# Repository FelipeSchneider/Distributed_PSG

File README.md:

# Distributed_PSG
Final project of the Electrical Engineering course, made by Felipe Britto Azevedo Schneider. The goal of this project is to develop hardware and software capable of monitoring a patient thought the night with more comfort that is possible using the traditional method.
Article abstract:
The impairment of sleep quality directly rises the chances of heart attack, obesity, and strokes, among others, what makes the polysomnography (PSG) an important public health tool. However, the inherent problems with PSG makes the correct diagnosis of sleep diseases a difficult task. This work presents a distributed novel class III PSG system, composed of three boards, all together capable of monitoring simultaneously environmental variables and patient signals. This system reduces the distress of a PSG exam, dismiss the need for an overnight sleep in a health care/sleep center, facilitates a self-set-up and an internet based diagnosis. Methods: Design and implementation of two wearable and one bedside PCB boards that together are able to, synchronously, monitor, process and log into a microSD card environmental parameters (temperature, humidity, visible light intensity and audible noise level) together with patient signals (electrocardiogram, electrooculogram, body, and limbs position). Results: A novel class III PSG system with independent boards capable of operating for more than 16 hours powered by a 750 mAh, 3.7 V battery with 0.003% data loss during preliminary PSG exams. Additionally, a computer-based program capable of reading, decode and present the data in graphs was developed and is presented. Conclusion: This article contributes to the PSG research and with the development of new PSG systems as well as the improvement of patients comfort. All code and hardware here developed are open.

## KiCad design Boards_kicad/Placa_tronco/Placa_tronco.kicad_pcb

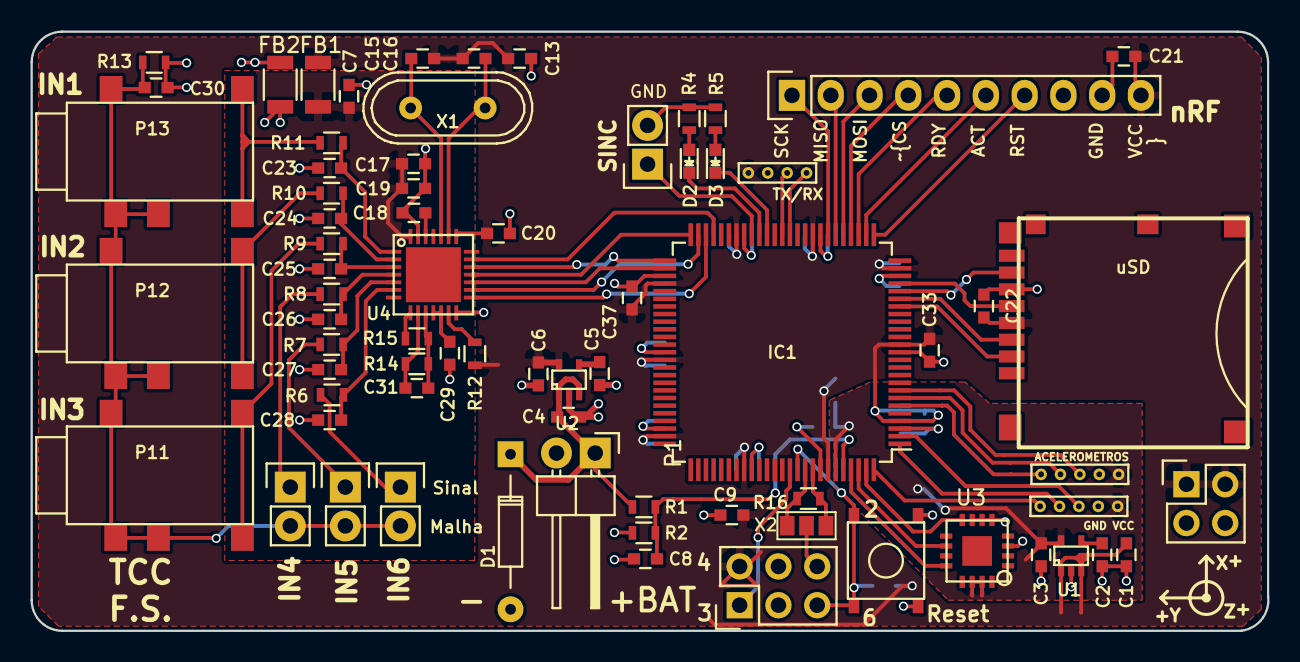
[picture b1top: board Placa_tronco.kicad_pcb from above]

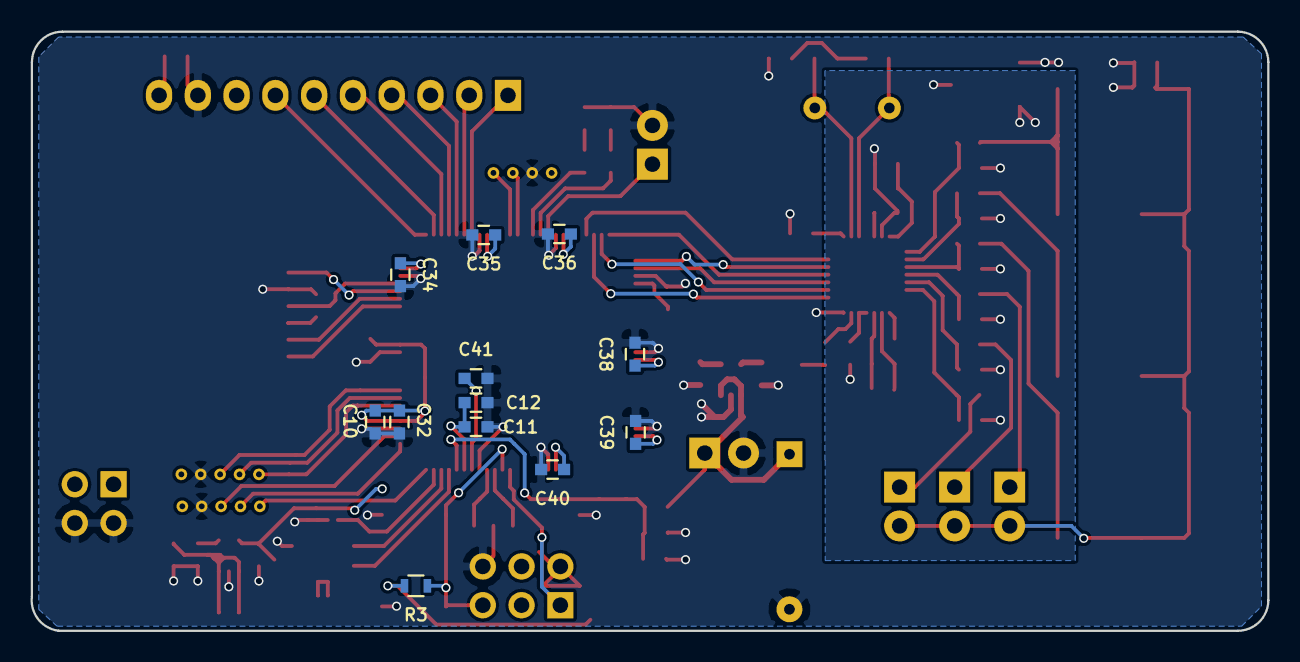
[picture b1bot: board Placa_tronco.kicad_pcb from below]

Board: 2 copper layers, 81.0 x 39.2 mm, 84 parts (12 on the bottom side), 67 nets.

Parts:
C1, C3, C4, C6, C7, C8: 1uF; C_0603
C2, C5, C11, C30: 10nF; C_0603
C9, C10, C17: 10u; C_0603
C12: 10uF; C_0603
C13, C19, C20, C29, C32, C33, C34, C35, C36, C37, C38, C39, C40, C41: 100n; C_0603
C15, C16: 22p; C_0603
C18: 1u; C_0603
C21, C22: 100nF; C_0603
C23, C24, C25, C26, C27, C28: Xn; C_0603
C31: 1.5n; C_0603
D1: Z 5.7V; Diode_DO-35_SOD27_Horizontal_RM10
D2, D3: LED; LED_0603
FB1, FB2: FILTER; R_1206
IC1: ATXMEGA128A1U-A; TQFP-100_14x14mm_Pitch0.5mm
P1: CONN_01X02; Pin_Header_Angled_1x02
P2: CONN_02X02; Pin_Header_Straight_2x02
P3: PDI; Pin_Header_Straight_2x03
P4, P5: Acelerometro; 5-pin-50mil
P6, P7, P8, P9: CONN_01X02; Pin_Header_Straight_1x02
P10: nRF8001 CON; Pin_Header_Straight_1x10
P11, P12, P13: MIC-CON-MONO; J2-connector
P14: CONN_01X04; 4-pin-50mil
R1, R2: 47k; R_0603
R3, R6, R7, R8, R9, R10, R11: 10K; R_0603
R4, R5: 220; R_0603
R12, R13, R14, R16: 1M; R_0603
R15: 100K; R_0603
SD1: uSD; uSD_5027_normal
SW1: SW_PUSH; 5mm-smd-button
U1: TPS71727; SC-70-5
U2: TPS71733; SC-70-5
U3: ADXL335; ADXL335_correto
U4: ADS1293; ADS1293-correto
X1: 4.096MHz; Crystal_HC49-U_Vertical
X2: CRISTAL_16MHz; CRISTAL_16Mhz

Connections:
+BAT: C4.2, D1.2, P1.1, R1.1, U2.1, U2.3
/ACT_nRF: IC1.27, P10.6
/ADCA_REF: C3.2, C11.2, C12.2, IC1.95, P4.1, P5.1, U1.5, U3.14, U3.15
/ADC_A1: C8.2, IC1.96, R1.2, R2.2
/ADC_A2: IC1.97, U3.12
/ADC_A3: IC1.98, U3.10
/ADC_A4: IC1.99, U3.8
/ADC_A5: IC1.100, P4.5
/ADC_A6: IC1.1, P4.4
/ADC_A7: IC1.2, P4.3
/ADC_B1: IC1.6, P5.5
/ADC_B2: IC1.7, P5.4
/ADC_B3: IC1.8, P5.3
/MISO_nRF: IC1.31, P10.2
/MISO_uSD: IC1.21, SD1.7
/MOSI-uSD: IC1.20, SD1.3
/MOSI_nRF: IC1.30, P10.3
/RDY_nRF: IC1.28, P10.5
/RESET: IC1.90, P3.5, R3.1, SW1.2
/RST_nRF: IC1.26, P10.7
/SCK-uSD: IC1.22, SD1.5
/SCK_nRF: IC1.32, P10.1
/malha: C30.2, P7.2, P8.2, P9.2, P11.1, P11.2, P11.5, P12.1, P12.2, P12.5, P13.1, P13.2, P13.5, R13.2
/xt1: IC1.91, R16.2, X2.1
/xt2: IC1.92, R16.1, X2.3
/~CS_nRF: IC1.29, P10.4
/~SS-uSD: IC1.19, SD1.2
GND: C1.1, C2.1, C3.1, C4.1, C5.1, C6.1, C8.1, C9.2, C10.2, C11.1, C12.1, C13.1, C20.2, C21.1, C22.1, C30.1, C32.2, C33.2, C34.2, C35.2, C36.2, C37.2, C38.2, C39.2, C40.2, C41.2, D1.1, FB2.1, IC1.3, IC1.13, IC1.23, IC1.33, IC1.43, IC1.53, IC1.63, IC1.73, IC1.84, IC1.93, P1.2, P2.3, P2.4, P3.6, P4.2, P5.2, P6.2, P10.9, P14.2, R2.1, R4.1, R5.1, R13.1, SD1.6, SW1.1, U1.2, U2.2, U3.3, U3.5, U3.6, U3.7, U4.14, X2.2
GNDA: C7.1, C17.2, C18.1, C19.2, C23.2, C24.2, C25.2, C26.2, C27.2, C28.2, C29.2, FB2.2, U4.27
unnamed: C2.2, U1.4
unnamed: C5.2, U2.4
unnamed: C15.2, U4.24, X1.2
unnamed: C16.2, U4.23, X1.1
unnamed: C18.2, U4.26
unnamed: C23.1, R11.1, U4.1
unnamed: C24.1, R10.1, U4.2
unnamed: C25.1, R9.1, U4.3
unnamed: C26.1, R8.1, U4.4
unnamed: C27.1, R7.1, U4.5
unnamed: C28.1, R6.1, U4.6
unnamed: C29.1, U4.11, U4.12
unnamed: C31.1, R14.1, R15.1, U4.10
unnamed: C31.2, R14.2, U4.9
unnamed: D2.1, IC1.41
unnamed: D2.2, R4.2
unnamed: D3.1, IC1.40
unnamed: D3.2, R5.2
unnamed: IC1.37, P14.4
unnamed: IC1.38, P14.3
unnamed: IC1.42, P6.1
unnamed: IC1.47, U4.20
unnamed: IC1.48, U4.15
unnamed: IC1.49, U4.16
unnamed: IC1.50, U4.18
unnamed: IC1.51, U4.19
unnamed: IC1.52, U4.17
unnamed: IC1.89, P3.1
unnamed: P7.1, R6.2
unnamed: P8.1, R7.2
unnamed: P9.1, R8.2
unnamed: P11.3, P11.4, R9.2
unnamed: P12.3, P12.4, R10.2
unnamed: P13.3, P13.4, R11.2
unnamed: R12.2, U4.13
unnamed: R15.2, U4.8
VCC: C1.2, C6.2, C9.1, C10.1, C13.2, C15.1, C16.1, C20.1, C21.2, C22.2, C32.1, C33.1, C34.1, C35.1, C36.1, C37.1, C38.1, C39.1, C40.1, C41.1, FB1.1, IC1.4, IC1.14, IC1.24, IC1.34, IC1.44, IC1.54, IC1.64, IC1.74, IC1.83, IC1.94, P2.1, P2.2, P3.2, P10.10, P14.1, R3.2, R12.1, SD1.4, U1.1, U1.3, U2.5, U4.22
aVDD: C7.2, C17.1, C19.1, FB1.2, U4.28

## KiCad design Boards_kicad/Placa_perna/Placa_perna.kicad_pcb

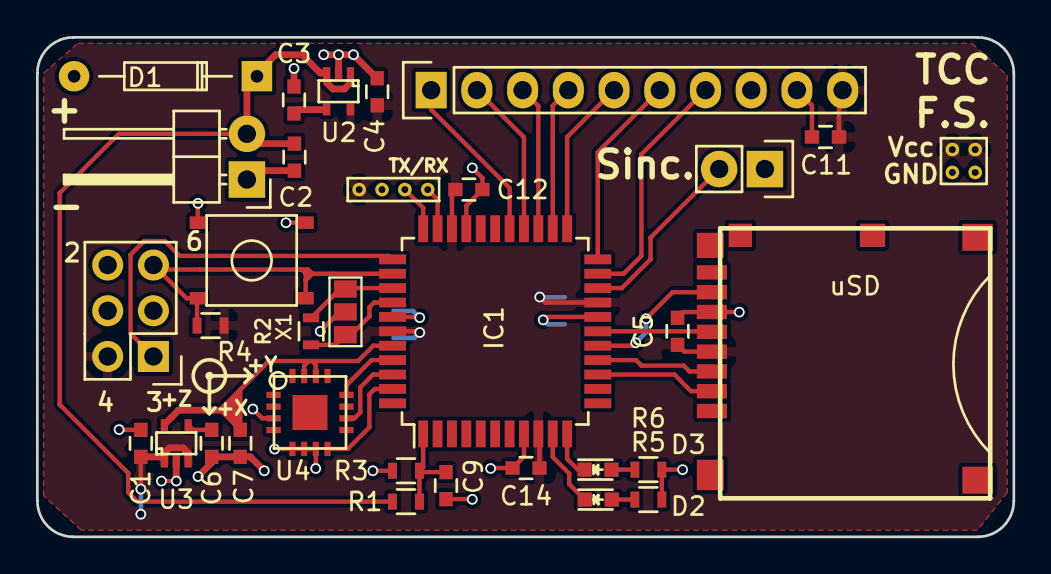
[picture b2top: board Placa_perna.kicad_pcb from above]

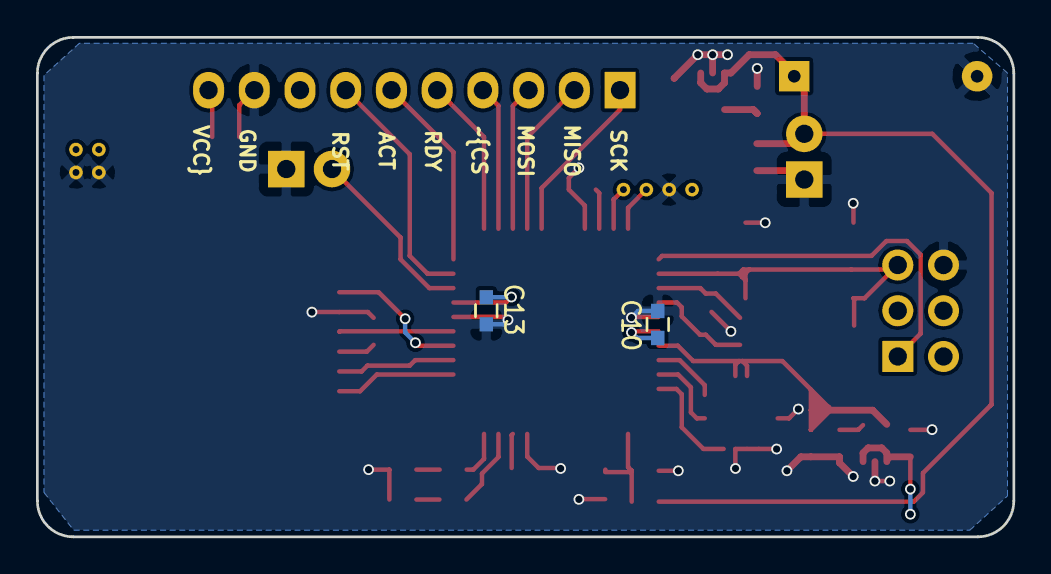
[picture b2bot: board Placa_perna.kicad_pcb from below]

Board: 2 copper layers, 54.2 x 27.8 mm, 35 parts (2 on the bottom side), 32 nets.

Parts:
C1, C2, C4, C7, C9: 1uF; C_0603
C3, C6: 10nF; C_0603
C5, C12, C13, C14: 100n; C_0603
C10: 10u; C_0603
C11: 100nF; C_0603
D1: Z 5.7V; Diode_DO-35_SOD27_Horizontal_RM10
D2, D3: LED; LED_0603
IC1: ATXMEGA128A4U-A; TQFP-44_10x10mm_Pitch0.8mm
P1: CONN_01X02; Pin_Header_Angled_1x02
P2: CONN_02X02; 2x2-pin-50mil
P3: PDI; Pin_Header_Straight_2x03
P4: CONN_01X04; 4-pin-50mil
P5: CONN_01X02; Pin_Header_Straight_1x02
P6: nRF8001 CON; Pin_Header_Straight_1x10
R1, R3: 47k; R_0603
R2: 1M; R_0603
R4: 10K; R_0603
R5, R6: 220; R_0603
SD1: uSD; uSD_5027_normal
SW1: SW_PUSH; 5mm-smd-button
U2: TPS71733; SC-70-5
U3: TPS71727; SC-70-5
U4: ADXL335; ADXL335_correto
X1: CRISTAL_16MHz; CRISTAL_16Mhz

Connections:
+BAT: C2.2, D1.2, P1.2, R1.1, U2.1, U2.3
/ACT_nRF: IC1.22, P6.6
/ADCA_REF: C7.2, IC1.40, U3.5, U4.14, U4.15
/ADC_A1: IC1.41, U4.12
/ADC_A2: IC1.42, U4.10
/ADC_A3: IC1.43, U4.8
/ADC_A5: C9.2, IC1.1, R1.2, R3.2
/MISO_nRF: IC1.26, P6.2
/MISO_uSD: IC1.16, SD1.7
/MOSI-uSD: IC1.15, SD1.3
/MOSI_nRF: IC1.25, P6.3
/RDY_nRF: IC1.23, P6.5
/RESET: IC1.35, P3.5, R4.1, SW1.2
/RST_nRF: IC1.21, P6.7
/SCK-uSD: IC1.17, SD1.5
/SCK_nRF: IC1.27, P6.1
/xt1: IC1.36, R2.2, X1.1
/xt2: IC1.37, R2.1, X1.3
/~CS_nRF: IC1.24, P6.4
/~SS-uSD: IC1.14, SD1.2
GND: C1.1, C2.1, C3.1, C4.1, C5.2, C6.1, C7.1, C9.1, C10.2, C11.1, C12.2, C13.2, C14.2, D1.1, IC1.8, IC1.18, IC1.30, IC1.38, P1.1, P2.3, P2.4, P3.6, P4.2, P5.1, P6.9, R3.1, R5.1, R6.1, SD1.6, SW1.1, U2.2, U3.2, U4.3, U4.5, U4.6, U4.7, X1.2
unnamed: C3.2, U2.4
unnamed: C6.2, U3.4
unnamed: D2.1, IC1.10
unnamed: D2.2, R5.2
unnamed: D3.1, IC1.11
unnamed: D3.2, R6.2
unnamed: IC1.20, P5.2
unnamed: IC1.32, P4.4
unnamed: IC1.33, P4.3
unnamed: IC1.34, P3.1
VCC: C1.2, C4.2, C5.1, C10.1, C11.2, C12.1, C13.1, C14.1, IC1.9, IC1.19, IC1.31, IC1.39, P2.1, P2.2, P3.2, P4.1, P6.10, R4.2, SD1.4, U2.5, U3.1, U3.3

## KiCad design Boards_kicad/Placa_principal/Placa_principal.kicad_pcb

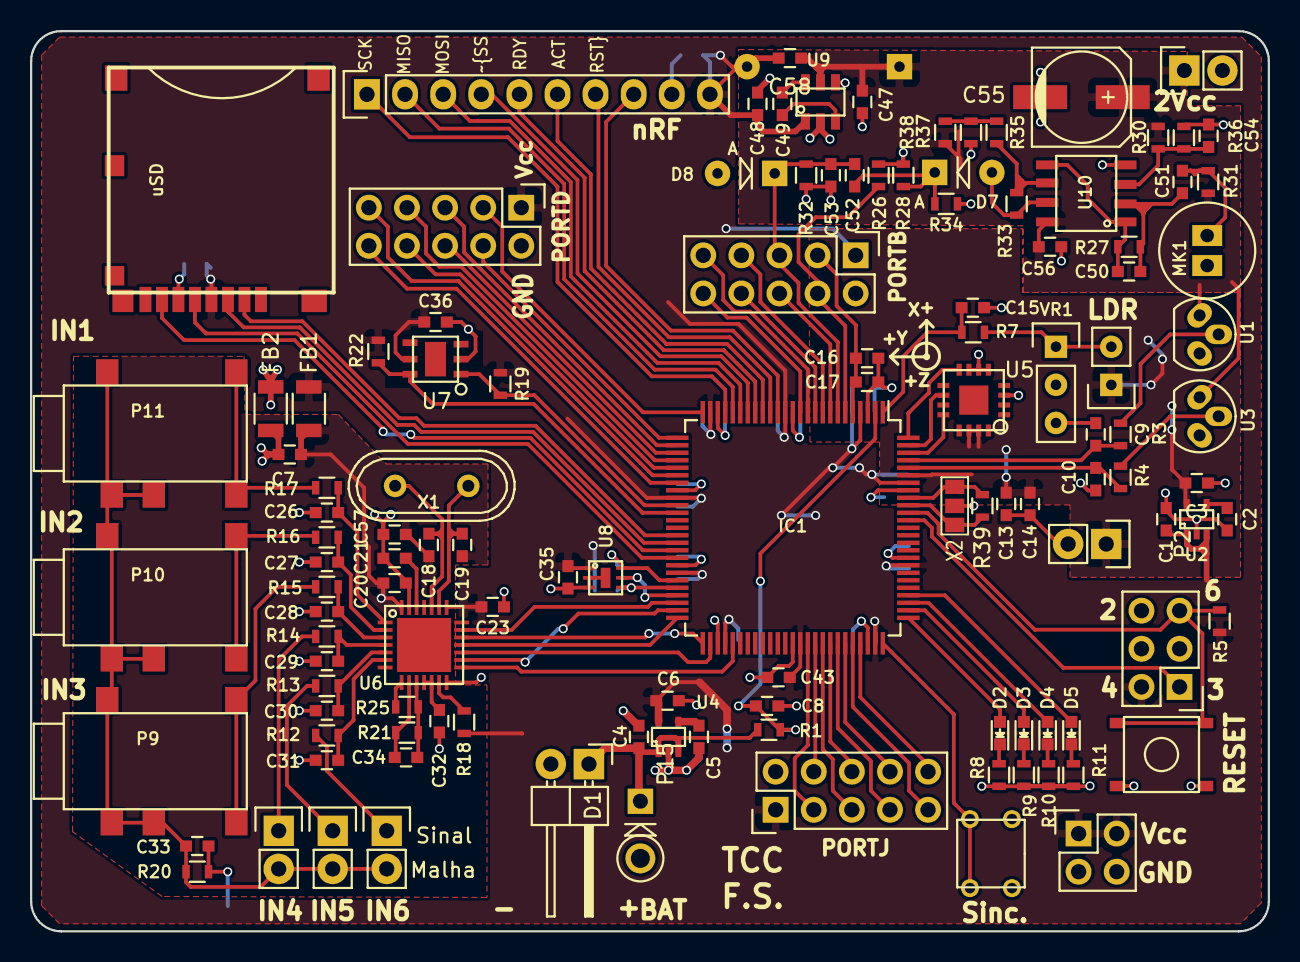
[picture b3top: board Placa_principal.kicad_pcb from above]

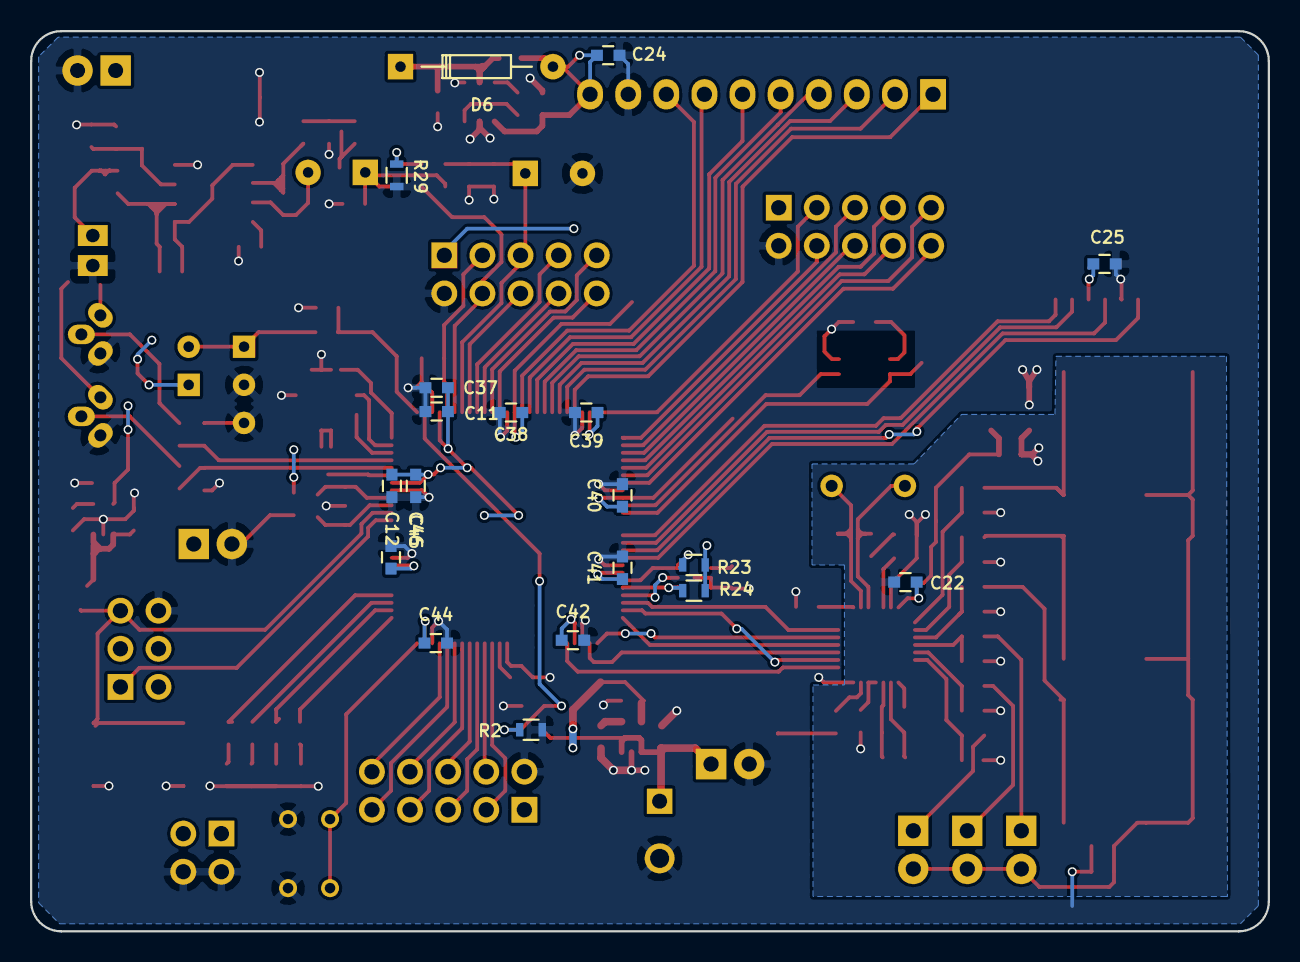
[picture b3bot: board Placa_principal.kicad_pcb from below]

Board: 2 copper layers, 82.5 x 60.0 mm, 140 parts (19 on the bottom side), 111 nets.

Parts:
C1, C3, C4, C6, C7, C8, C15: 1uF; C_0603
C2, C5, C13, C16, C33: 10nF; C_0603
C9, C10, C14, C17, C58: 10uF; C_0603
C11, C12, C20: 10u; C_0603
C18, C19: 22p; C_0603
C21: 1u; C_0603
C22, C23, C32, C35, C36, C37, C38, C39, C40, C41, C42, C43, C44, C45, C46, C56, C57: 100n; C_0603
C24, C25: 100nF; C_0603
C26, C27, C28, C29, C30, C31: Xn; C_0603
C34: 1.5n; C_0603
C47, C48, C49: 3u3; C_0603
C50: 16pF; C_0603
C51, C54: 2u2F; C_0603
C52, C53: 1u5F; C_0603
C55: 47uF; c_elec_6.3x7.7
D1: Z 5.7V; Diode_DO-41_SOD81_Vertical_KathodeUp
D2, D3, D4, D5: LED; LED_0603
D6: D_Schottky; Diode_DO-35_SOD27_Horizontal_RM10
D7, D8: D_Schottky; Diode_DO-41_SOD81_Vertical_AnodeUp
FB1, FB2: FILTER; R_1206
IC1: ATXMEGA128A1U-A; TQFP-100_14x14mm_Pitch0.5mm
MK1: Electret-mic; Eletret-mic-6x5
P1: CONN_02X02; Pin_Header_Straight_2x02
P2, P12, P13, P14, P16: CONN_01X02; Pin_Header_Straight_1x02
P3: PDI; Pin_Header_Straight_2x03
P4: PORT B; Pin_Header_Straight_2x05
P5: PORT J; Pin_Header_Straight_2x05
P6: PORT D; Pin_Header_Straight_2x05
P8: nRF8001 CON; Pin_Header_Straight_1x10
P9, P10, P11: MIC-CON-MONO; J2-connector
P15: CONN_01X02; Pin_Header_Angled_1x02
R1, R2, R33: 47k; R_0603
R3, R4: 15k; R_0603
R5, R12, R13, R14, R15, R16, R17, R19, R22, R23, R24, R26: 10K; R_0603
R6: LDR; Pin_Header_Straight_1x02
R7: 8k2; R_0603
R8, R9, R10, R11: 220; R_0603
R18, R20, R21, R39: 1M; R_0603
R25: 100K; R_0603
R27: 120k; R_0603
R28, R29, R30, R32, R36: 100k; R_0603
R31: 12k; R_0603
R34: 180k; R_0603
R35, R38: 10k; R_0603
R37: 22k; R_0603
SD1: uSD; uSD_5027_normal
SW1: SW_PUSH; 5mm-smd-button
SW2: SW_PUSH; 4.5mm-dip-button
U1, U3: LM35; TO-92_Molded_Narrow_Oval
U2: TPS71727; SC-70-5
U4: TPS71733; SC-70-5
U5: ADXL335; ADXL335_correto
U6: ADS1293; ADS1293-correto
U7: HDC1050
U8: OPT3001
U9: LM2665; DBV-PDSO-G6
U10: opa2333; SOIC8-PDSO_G8
VR1: 100k; Pin_Header_Straight_1x03
X1: 4.096MHz; Crystal_HC49-U_Vertical
X2: CRISTAL_16MHz; CRISTAL_16Mhz

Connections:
+BAT: C4.2, D1.2, P15.1, R1.1, U4.1, U4.3
/2Vcc: C47.1, C55.1, C56.1, C58.1, D6.1, P16.1, R30.1, R31.1, R38.1, U1.1, U3.1, U9.5, U10.8
/8_nRF: IC1.15, P8.8
/ACT_nRF: IC1.17, P8.6
/ADCA_REF: C3.2, C13.2, C14.2, IC1.95, P2.1, R6.1, U2.5, U5.14, U5.15
/ADCB_REF: C16.2, C17.2, IC1.5, P4.3
/ADC_A1: C10.2, IC1.96, R4.2
/ADC_A2: C9.2, IC1.97, R3.2
/ADC_A3: IC1.98, U5.12
/ADC_A4: IC1.99, U5.10
/ADC_A5: IC1.100, U5.8
/ADC_A6: C15.2, IC1.1, R7.1
/ADC_A7: C8.2, IC1.2, R1.2, R2.2
/ADC_B1: IC1.6, P4.4, R26.2
/ADC_B2: C52.1, C53.1, D8.1, IC1.7, P4.5, R32.1
/ADC_B3: IC1.8, P4.6
/ADC_B4: IC1.9, P4.7
/ADC_B5: IC1.10, P4.8
/ADC_B6: IC1.11, P4.9
/ADC_B7: IC1.12, P4.10
/INT_OPT: IC1.47, U8.5
/J0: IC1.65, P5.3
/J1: IC1.66, P5.4
/J2: IC1.67, P5.5
/J3: IC1.68, P5.6
/J4: IC1.69, P5.7
/J5: IC1.70, P5.8
/J6: IC1.71, P5.9
/J7: IC1.72, P5.10
/MISO_nRF: IC1.21, P8.2
/MISO_uSD: IC1.41, SD1.7
/MOSI-uSD: IC1.40, SD1.3
/MOSI_nRF: IC1.20, P8.3
/RDY_nRF: IC1.18, P8.5
/RESET: IC1.90, P3.5, R5.1, SW1.2
/RST_nRF: IC1.16, P8.7
/SCK-uSD: IC1.42, SD1.5
/SCK_nRF: IC1.22, P8.1
/SCL_HDC: IC1.36, R22.1, U7.6
/SCL_OPT: IC1.46, R24.2, U8.4
/SDA_HDC: IC1.35, R19.2, U7.1
/SDA_OPT: IC1.45, R23.2, U8.6
/malha: C33.2, P9.1, P9.2, P9.5, P10.1, P10.2, P10.5, P11.1, P11.2, P11.5, P12.2, P13.2, P14.2, R20.2
/xt1: IC1.91, R39.2, X2.1
/xt2: IC1.92, R39.1, X2.3
/~CS_nRF: IC1.19, P8.4
/~SS-uSD: IC1.39, SD1.2
GND: C1.1, C2.1, C3.1, C4.1, C5.1, C6.1, C8.1, C9.1, C10.1, C11.2, C12.2, C13.1, C14.1, C15.1, C16.1, C17.1, C23.2, C24.1, C25.1, C33.1, C35.2, C36.2, C37.2, C38.2, C39.2, C40.2, C41.2, C42.2, C43.2, C44.2, C45.2, C46.2, C47.2, C48.2, C53.2, C54.2, C55.2, C56.2, D1.1, D8.2, FB2.1, IC1.3, IC1.13, IC1.23, IC1.33, IC1.43, IC1.53, IC1.63, IC1.73, IC1.84, IC1.93, MK1.2, P1.3, P1.4, P2.2, P3.6, P4.2, P5.2, P6.2, P8.9, P15.2, P16.2, R2.1, R8.1, R9.1, R10.1, R11.1, R20.1, R29.1, R32.2, R34.2, R36.2, R37.1, SD1.6, SW1.1, SW2.1, U1.3, U2.2, U3.3, U4.2, U5.3, U5.5, U5.6, U5.7, U6.14, U7.2, U8.0, U8.2, U8.3, U9.2, U9.4, U10.4, VR1.2, VR1.3, X2.2
GNDA: C7.1, C20.2, C21.1, C22.2, C26.2, C27.2, C28.2, C29.2, C30.2, C31.2, C32.2, C57.2, FB2.2, U6.27
unnamed: C2.2, U2.4
unnamed: C5.2, U4.4
unnamed: C18.2, U6.24, X1.2
unnamed: C19.2, U6.23, X1.1
unnamed: C21.2, U6.26
unnamed: C26.1, R17.1, U6.1
unnamed: C27.1, R16.1, U6.2
unnamed: C28.1, R15.1, U6.3
unnamed: C29.1, R14.1, U6.4
unnamed: C30.1, R13.1, U6.5
unnamed: C31.1, R12.1, U6.6
unnamed: C32.1, U6.11, U6.12
unnamed: C34.1, R21.1, R25.1, U6.10
unnamed: C34.2, R21.2, U6.9
unnamed: C49.1, U9.3
unnamed: C49.2, U9.6
unnamed: C50.1, R27.1, U10.1, U10.5
unnamed: C50.2, C51.2, R27.2, U10.2
unnamed: C51.1, MK1.1, R31.2
unnamed: C52.2, D7.1, R28.1, R34.1
unnamed: C54.1, R30.2, R36.1, U10.3
unnamed: D2.1, IC1.76
unnamed: D2.2, R8.2
unnamed: D3.1, IC1.77
unnamed: D3.2, R9.2
unnamed: D4.1, IC1.78
unnamed: D4.2, R10.2
unnamed: D5.1, IC1.79
unnamed: D5.2, R11.2
unnamed: D7.2, R33.1, U10.7
unnamed: IC1.25, P6.3
unnamed: IC1.26, P6.4
unnamed: IC1.27, P6.5
unnamed: IC1.28, P6.6
unnamed: IC1.29, P6.7
unnamed: IC1.30, P6.8
unnamed: IC1.31, P6.9
unnamed: IC1.32, P6.10
unnamed: IC1.48, U6.20
unnamed: IC1.49, U6.16
unnamed: IC1.50, U6.18
unnamed: IC1.51, U6.19
unnamed: IC1.52, U6.17
unnamed: IC1.55, U6.15
unnamed: IC1.75, SW2.2
unnamed: IC1.89, P3.1
unnamed: P9.3, P9.4, R15.2
unnamed: P10.3, P10.4, R16.2
unnamed: P11.3, P11.4, R17.2
unnamed: P12.1, R12.2
unnamed: P13.1, R13.2
unnamed: P14.1, R14.2
unnamed: R3.1, U1.2
unnamed: R4.1, U3.2
unnamed: R6.2, R7.2, VR1.1
unnamed: R18.2, U6.13
unnamed: R25.2, U6.8
unnamed: R26.1, R28.2, R29.2
unnamed: R33.2, R35.1, U10.6
unnamed: R35.2, R37.2, R38.2
VCC: C1.2, C6.2, C11.1, C12.1, C23.1, C24.2, C25.2, C35.1, C36.1, C37.1, C38.1, C39.1, C40.1, C41.1, C42.1, C43.1, C44.1, C45.1, C46.1, C48.1, C58.2, D6.2, FB1.1, IC1.4, IC1.14, IC1.24, IC1.34, IC1.44, IC1.54, IC1.64, IC1.74, IC1.83, IC1.94, P1.1, P1.2, P3.2, P4.1, P5.1, P6.1, P8.10, R5.2, R18.1, R19.1, R22.2, R23.1, R24.1, SD1.4, U2.1, U2.3, U4.5, U6.22, U7.5, U8.1, U9.1
aVDD: C7.2, C18.1, C19.1, C20.1, C22.1, C57.1, FB1.2, U6.28

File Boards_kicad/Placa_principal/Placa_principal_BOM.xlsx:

Id | Designator | Package | Quantity | Designation | Supplier and ref |  |  | posicionados
1 | R25 | R_0603 | 1 | 100K |  |  |  | R25
2 | R19,R22,R23,R24 | R_0603 | 4 | 1K2 |  |  |  | R19, R22
3 | ,, | 1pin | 3
4 | P4 | Pin_Header_Straight_2x05 | 1 | PORT A
5 | C16,C2,C5,C13,C33 | C_0603 | 5 | 10nF |  |  |  | C2,C5,C22
6 | C37,C22,C23,C32,C35,C36,C38,C39,C40,C41,C42,C43,C44,C45,C46 | C_0603 | 15 | 100n |  |  |  | C35,C23,C32
7 | P6 | Pin_Header_Straight_2x05 | 1 | PORT D
8 | U3,U1 | TO-92_Molded_Narrow_Oval | 2 | LM35
9 | X1 | Crystal_HC49-U_Vertical | 1 | 4.096MHz
10 | IC1 | TQFP-100_14x14mm_Pitch0.5mm | 1 | ATXMEGA128A1U-A
11 | C9,C10,C14,C17 | C_0603 | 4 | 10uF
12 | C1,C3,C4,C6,C7,C8,C15 | C_0603 | 7 | 1uF |  |  |  | C1,C3,C4,C6,C7
13 | C11,C12,C20 | C_0603 | 3 | 10u |  |  |  | C20
14 | C18,C19 | C_0603 | 2 | 22p |  |  |  | C18,C19
15 | C21 | C_0603 | 1 | 1u
16 | C24,C25 | C_0603 | 2 | 100nF
17 | C26,C27,C28,C29,C30,C31 | C_0603 | 6 | Xn
18 | C34 | C_0603 | 1 | 1.5n |  |  |  | C34
19 | D1 | Diode_DO-35_SOD27_Horizontal_RM10 | 1 | Z 5.7V
20 | D2,D3,D4,D5 | LED_0603 | 4 | LED |  |  |  | D2,D3,D4,D5
21 | FB1,FB2 | R_0805 | 2 | FILTER
22 | P1 | Pin_Header_Straight_2x02 | 1 | CONN_02X02
23 | P3 | Pin_Header_Straight_2x03 | 1 | PDI
24 | P5 | Pin_Header_Straight_2x05 | 1 | PORT J
25 | P8 | Pin_Header_Straight_1x10 | 1 | nRF8001 CON
26 | R1,R2,R33 | R_0603 | 3 | 47k
27 | R3,R4 | R_0603 | 2 | 15k
28 | R5,R12,R13,R14,R15,R16,R17,R26 | R_0603 | 8 | 10K |  |  |  | R12,R13,R14,R15,R16,R17
29 | R7 | R_0603 | 1 | 8k2
30 | R8,R9,R10,R11 | R_0603 | 4 | 220 |  |  |  | R8,R9,R10,R11
31 | R18,R20,R21 | R_0603 | 3 | 1M |  |  |  | R18,R21
32 | U2 | SC-70-5 | 1 | TPS71727
33 | U4 | SC-70-5 | 1 | TPS71733
34 | U5 | ADXL335 | 1 | ADXL335 |  |  |  | X
35 | U6 | ADS1293 | 1 | ADS1293 |  |  |  | X
36 | U7 | HDC1000 | 1 | HDC1000 |  |  |  | X
37 | U8 | OPT3001 | 1 | OPT3001
38 | VR1 | Pin_Header_Straight_1x03 | 1 | 100k
39 | P15,P12,P13,P14,P16 | Pin_Header_Straight_1x02 | 5 | CONN_01X02
40 | R6 | Pin_Header_Straight_1x02 | 1 | LDR
41 | SD1 | uSD_5027_normal | 1 | uSD |  |  |  | SD1
42 | P9,P10,P11 | J2-connector | 3 | MIC-CON-MONO |  |  |  | P9,P10,P11
43 | SW1 | 5mm-smd-button | 1 | SW_PUSH |  |  |  | SW1
44 | SW2 | 4.5mm-dip-button | 1 | SW_PUSH |  |  |  | SW2
45 | C47,C48,C49 | C_0603 | 3 | 3u3 |  |  |  | c47,c49
46 | C50 | C_0603 | 1 | 16pF |  |  |  | C50
47 | C51,C54 | C_0603 | 2 | 2u2F |  |  |  | C51,C54
48 | C52,C53 | C_0603 | 2 | 1u5F |  |  |  | C52,C53
49 | D6 | Diode_DO-35_SOD27_Horizontal_RM10 | 1 | D_Schottky
50 | D7,D8 | Diode_DO-41_SOD81_Vertical_AnodeUp | 2 | D_Schottky
51 | MK1 | Eletret-mic-6x5 | 1 | Electret-mic
52 | R27 | R_0603 | 1 | 120k
53 | R28,R29,R30,R32,R36 | R_0603 | 5 | 100k
54 | R31 | R_0603 | 1 | 12k
55 | R34 | R_0603 | 1 | 180k
56 | R35,R38 | R_0603 | 2 | 10k
57 | R37 | R_0603 | 1 | 22k
58 | U9 | DBV-PDSO-G6 | 1 | LM2665
59 | U10 | SOIC8-PDSO_G8 | 1 | opa2333

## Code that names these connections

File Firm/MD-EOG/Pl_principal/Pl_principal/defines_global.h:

/*
 * defines_global.h
 *
 * Created: 16-Mar-16 10:03:14
 *  Author: Felipe Schneider
 */ 


#ifndef DEFINES_GLOBAL_H_
#define DEFINES_GLOBAL_H_

#define lo8(x) ((uint8_t)((x) & 0xff))
#define hi8(x) ((uint8_t)((x & 0xff00)>>8))
#define hi16(x) ((uint8_t)((x & 0xff0000)>>16))
#define hi24(x) ((uint8_t)((x & 0xff000000)>>24))

#define F_CPU			32000000UL		//CPU CLOCK (for delay lib)
//#define XT_CLOCK						//Enables the external XT init functions (btw 12 an 16MHz with the actual settings)
//#define PLL_CLOCK						//Enables the PLL init functions (external xt necessary)
#define RC_32_CLOCK						//Enables the internal resonator init functions (32MHz with PLL with the actual settings)
#define	SERIAL_D0						//Enables the Uart D0 init functions
#define ZERO_ASCII		48

#define READ_ADS	0x80
#define WRITE_ADS	0x00

#define	VALOR_A_TENSAO	0.001340814115672
#define	VALOR_B_TENSAO	-0.274399010115506

#define HEADER_1	0x53	//S em ascii
#define HEADER_2	0x54	//T em ascii

// Connected to port A
#define REFA_PIN	PIN0_bm
#define LM35_1_OUT	PIN1_bm
#define LM35_2_OUT	PIN2_bm
#define XOUT_ADXL	PIN3_bm
#define YOUT_ADXL	PIN4_bm
#define ZOUT_ADXL	PIN5_bm
#define LDR_OUT		PIN6_bm
#define BAT_DIV		PIN7_bm

// Connected to port B
#define REFB_PIN	PIN0_bm
#define SOUND_1_OUT	PIN1_bm				//probably the best place to analise the ambient sound noise 
#define SOUND_2_OUT	PIN2_bm

// Connected to port C
#define PIN_8_nRF	PIN0_bm
#define RST_nRF		PIN1_bm
#define ACT_nRF		PIN2_bm
#define RDY_nRF		PIN3_bm
#define CS_nRF		PIN4_bm
#define MOSI_nRF	PIN5_bm
#define MISO_nRF	PIN6_bm
#define SCK_nRF		PIN7_bm

// Connected to port E
#define SDA_HDC		PIN0_bm
#define SCL_HDC		PIN1_bm
#define DRDY_HDC	PIN2_bm

#define SS_uSD		PIN4_bm
#define MOSI_uSD	PIN5_bm	
#define MISO_uSD	PIN6_bm	
#define SCK_uSD		PIN7_bm	

// Connected to port F
#define SDA_OPT		PIN0_bm
#define SCL_OPT		PIN1_bm
#define INT_OPT		PIN2_bm
#define DRDYB_ADS	PIN3_bm
#define SS_ADS		PIN4_bm
#define MOSI_ADS	PIN5_bm
#define MISO_ADS	PIN6_bm
#define SCK_ADS		PIN7_bm

// Connected to port H

#define ALARM_ADS	PIN0_bm

// Connected to port K
#define SINC_BOT	PIN0_bm
#define LED_2		PIN1_bm
#define LED_3		PIN2_bm
#define LED_4		PIN3_bm
#define LED_5		PIN4_bm

#endif /* DEFINES_GLOBAL_H_ */

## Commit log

2017-09-22 Just moving files.
2017-11-07 RBE Journal version.
